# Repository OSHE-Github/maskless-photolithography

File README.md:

# Maskless Photolithography

*･゜ﾟ･*:.｡..｡.:*･'(*ﾟ▽ﾟ*)'･*:.｡. .｡.:*･゜ﾟ･*

## Copyright

- All code is licensed under the GPL 3.0 or later. You can view a copy of this license in LICENSE.code
- All hardware computer aided design "CAD files" are licensed under the CERN-OHL-S license. A copy of this license can be found in LICENSE.cad
- Some footprints are provided by the manufacturer or a third party source. They are licensed under their respective licenses.

Which licenses apply to which files will be clarified in a later commit. If you have questions please contact us.

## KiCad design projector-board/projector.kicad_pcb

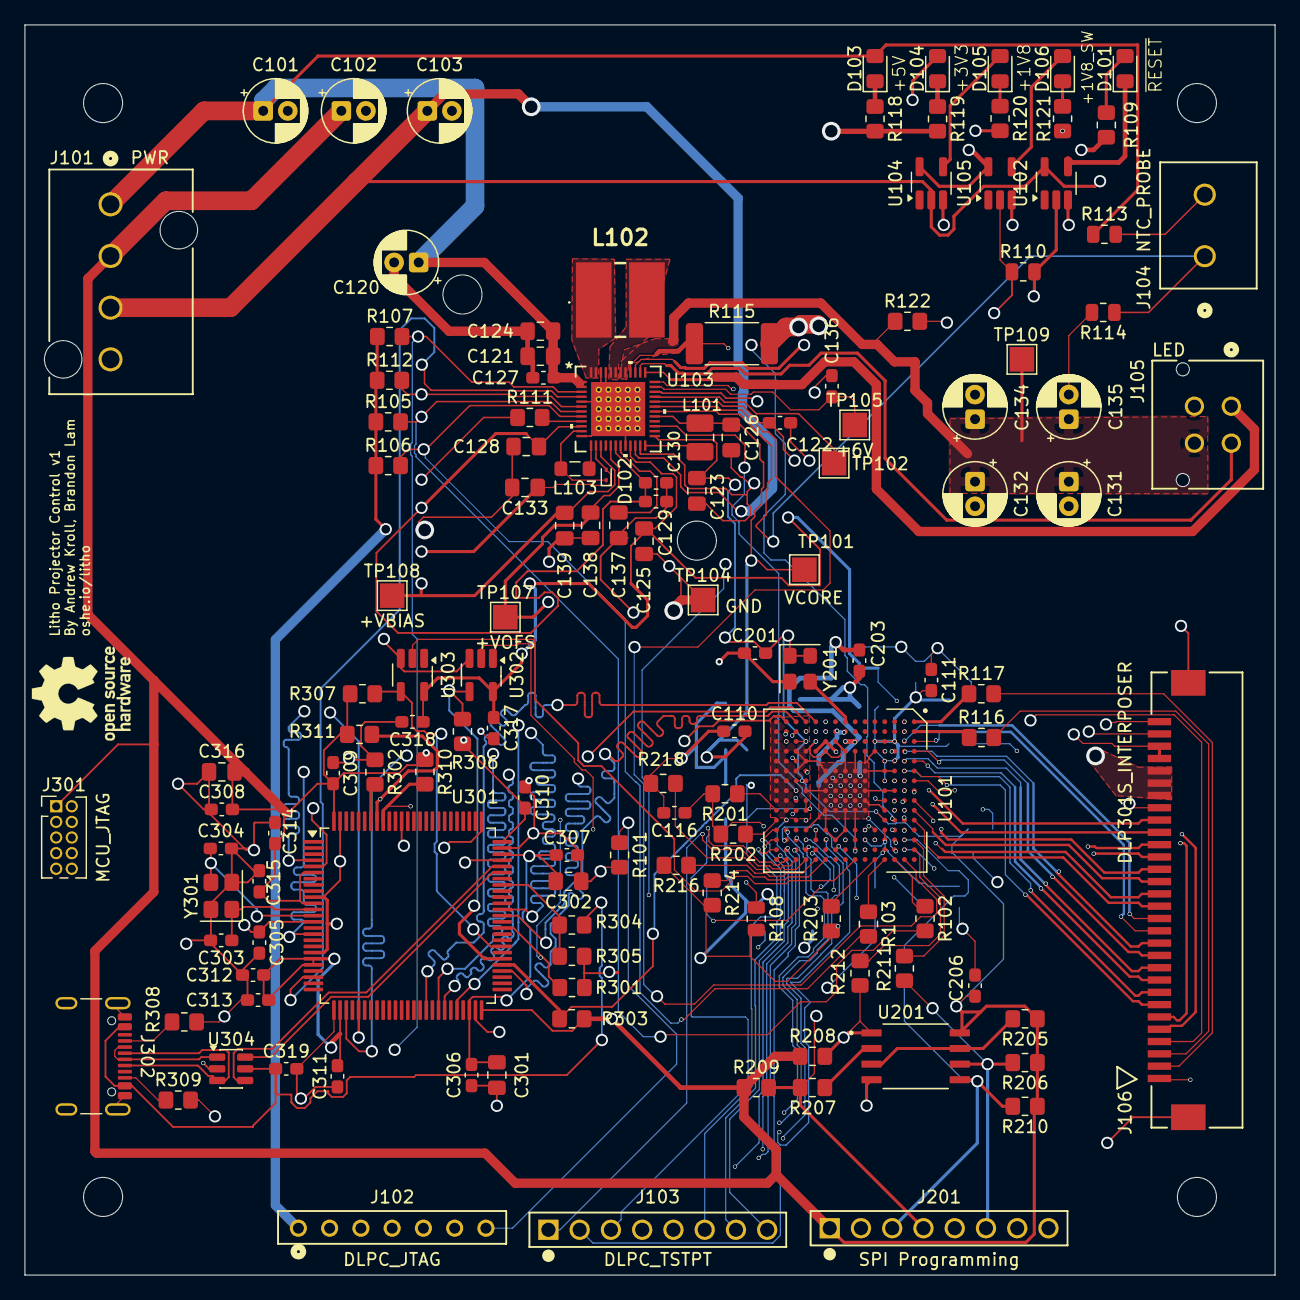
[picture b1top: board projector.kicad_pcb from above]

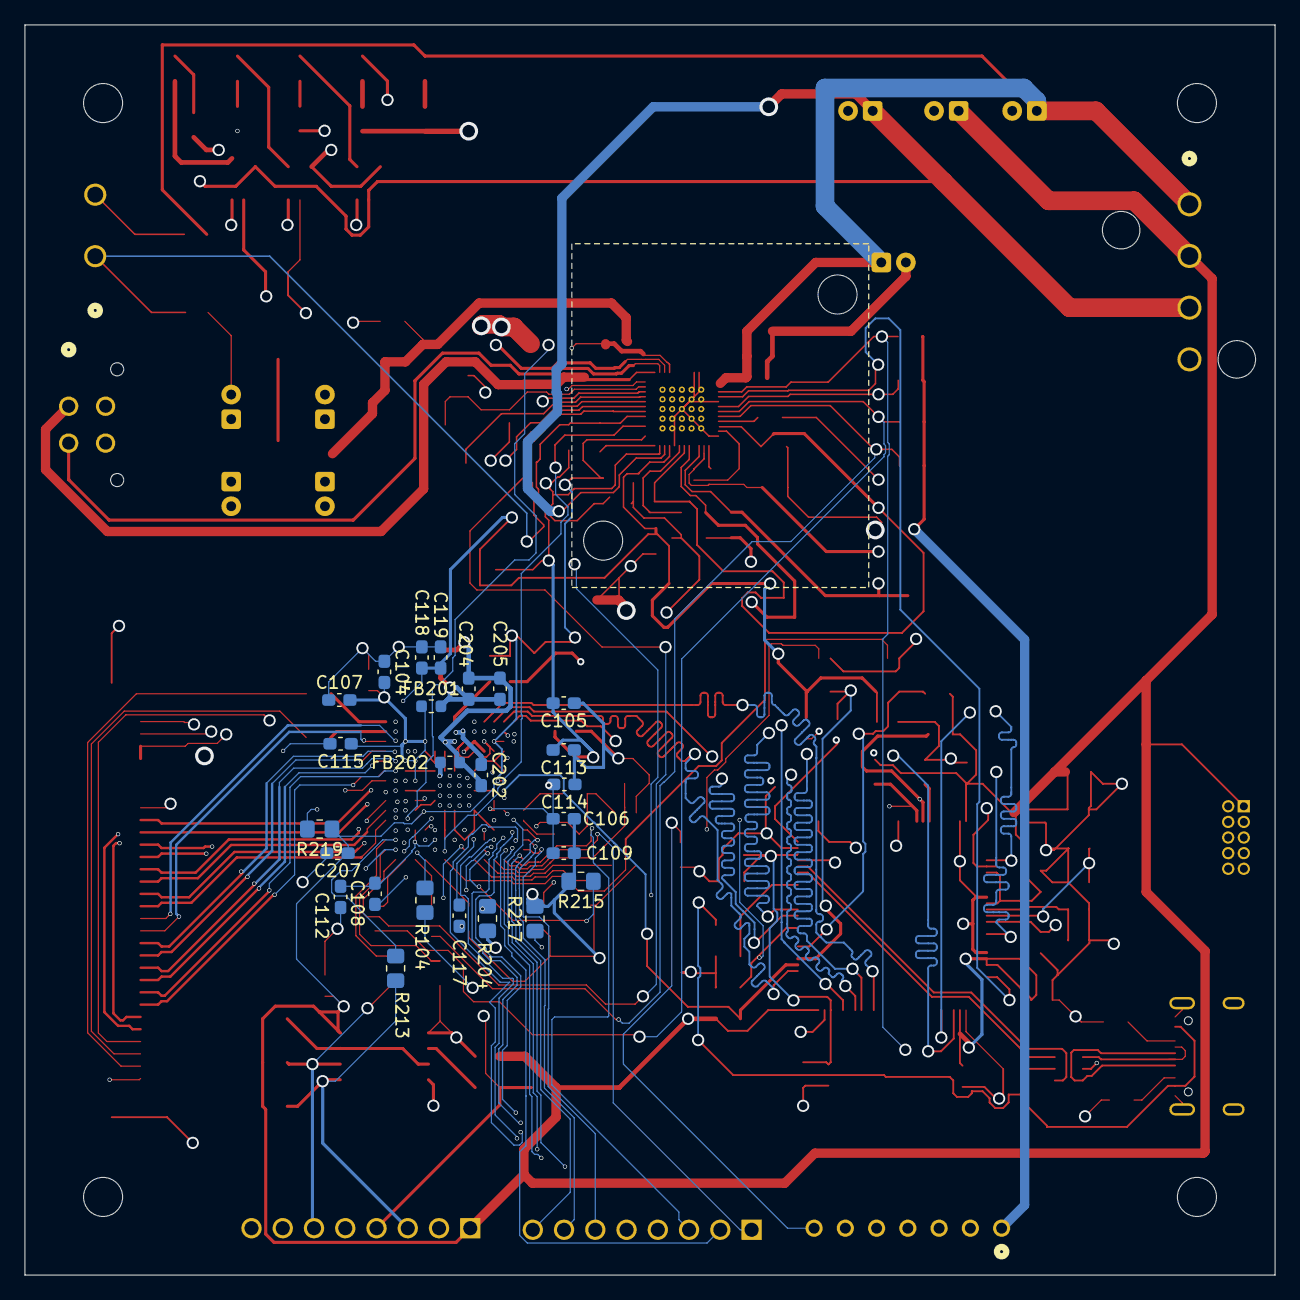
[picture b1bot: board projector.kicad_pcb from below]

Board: 4 copper layers, 101.6 x 101.6 mm, 156 parts (25 on the bottom side), 140 nets.

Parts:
C101, C102, C103: 47uF; CP_Radial_D5.0mm_P2.00mm
C104, C127, C129, C308: 1uF; C_0603_1608Metric_Pad1.08x0.95mm_HandSolder
C105, C106, C107, C108, C109, C110, C111, C112, C113, C114, C115, C116, C117, C118, C119, C122, C130, C136, C201, C203, C205, C206, C207, C305, C309, C310, C311, C312, C313, C314, C315: 0.1uF; C_0603_1608Metric_Pad1.08x0.95mm_HandSolder
C120, C131, C132, C134, C135: 22uF; CP_Radial_D5.0mm_P2.00mm
C121, C124, C125, C126, C128: 10uF; C_0805_2012Metric_Pad1.18x1.45mm_HandSolder
C123, C137, C301, C302: 2.2uF; C_0805_2012Metric_Pad1.18x1.45mm_HandSolder
C133, C138, C139: 0.22uF; C_0805_2012Metric_Pad1.18x1.45mm_HandSolder
C202, C204: 0.01uF; C_0603_1608Metric_Pad1.08x0.95mm_HandSolder
C303, C304: 12pF; C_0603_1608Metric_Pad1.08x0.95mm_HandSolder
C306, C307, C317, C318, C319: 100nF; C_0603_1608Metric_Pad1.08x0.95mm_HandSolder
C316: 4.7uF; C_0805_2012Metric_Pad1.18x1.45mm_HandSolder
D101, D103, D104, D105, D106: RED; D_0805_2012Metric_Pad1.15x1.40mm_HandSolder
D102: RB720M-30_R1_00001; D_SOD-923
FB201, FB202: BLM18EG601SN1D; L_0603_1608Metric
J101: PWR; CONN_55660001-SD_04_MOL
J102: DLPC_JTAG; CON7_1X7_TU_TSW
J103: DLPC_TSTPT; CONN8_61300811121_WRE
J104: NTC_PROBE; CONN2_710002_WRE
J105: LED; CONN_SD-43045-010_04_MOL
J106: DMD; CON_522713079_MOL
J201: SPI Programming; CONN8_61300811121_WRE
J301: MCU_JTAG; PinHeader_2x05_P1.27mm_Vertical
J302: USB4105-GF-A; USB_C_Receptacle_GCT_USB4105-xx-A_16P_TopMnt_Horizontal
L101: 2.2uH; L_1008_2520Metric_Pad1.43x2.20mm_HandSolder
L102: 2.2uH; SDCHA1V60451R2R
L103: 10uH; L_0805_2012Metric_Pad1.05x1.20mm_HandSolder
R101, R112, R301, R302, R306, R307: 10k; R_0805_2012Metric_Pad1.20x1.40mm_HandSolder
R102, R103, R104, R111, R207, R211, R212, R213: 30.1; R_0805_2012Metric_Pad1.20x1.40mm_HandSolder
R105, R106, R107, R122: 100k; R_0805_2012Metric_Pad1.20x1.40mm_HandSolder
R108: 0; R_0805_2012Metric
R109, R118, R119, R120, R121: 510; R_0805_2012Metric_Pad1.20x1.40mm_HandSolder
R110, R113, R114: DNL; R_0805_2012Metric
R115: 39m, 3 W; R_2512_6332Metric_Pad1.40x3.35mm_HandSolder
R116, R117: 43; R_0805_2012Metric_Pad1.20x1.40mm_HandSolder
R201, R202, R203, R204, R205, R206, R208, R209, R210, R214, R215, R216, R217, R218, R219, R303, R310, R311: 4.7k; R_0805_2012Metric_Pad1.20x1.40mm_HandSolder
R304: 33k; R_0805_2012Metric_Pad1.20x1.40mm_HandSolder
R305: 82k; R_0805_2012Metric_Pad1.20x1.40mm_HandSolder
R308, R309: 5.1k; R_0805_2012Metric_Pad1.20x1.40mm_HandSolder
TP101: VCORE; TestPoint_Pad_2.0x2.0mm
TP102: SENS1; TestPoint_Pad_2.0x2.0mm
TP104: GND; TestPoint_Pad_2.0x2.0mm
TP105: +6V; TestPoint_Pad_2.0x2.0mm
TP107: +VOFS; TestPoint_Pad_2.0x2.0mm
TP108: +VBIAS; TestPoint_Pad_2.0x2.0mm
TP109: VLED; TestPoint_Pad_2.0x2.0mm
U101: DLPC1438; NFBGA201
U102, U104, U105, U302, U303: SN74AUP1G07DBVR; SOT-23-5_HandSoldering
U103: DLPA2005ERSLR; RSL48_4P4X4P4_TEX
U201: AT25SF321B-SHB-T; SOIC127P790X216-8N
U301: STM32H7B0VBTx; LQFP-100_14x14mm_P0.5mm
U304: USBLC6-2SC6; SOT-23-6
Y201: ASE-24.000MHZ-L-C-T; Oscillator_SMD_Abracon_ASE-4Pin_3.2x2.5mm
Y301: 25MHz; Crystal_SMD_3225-4Pin_3.2x2.5mm

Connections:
+1V8_SRC: C103.1, J101.3, U102.5 (VCC), U103.22 (LS_IN), U104.2 (A)
+1V8_SW: C116.1, C117.1, C118.1, C119.1, C122.2, C125.1, C317.1, C318.1, J102.1, J106.27, J106.28, R105.1, R106.1, R107.1, R110.1, R112.1, R201.2, R202.2, U101.C7 (VCC18), U101.C9 (VCC18), U101.D4 (VCC18), U101.E12 (VCC18), U101.F12 (VCC18), U101.K13 (VCC18), U101.M11 (VCC18), U103.21 (LS_OUT), U103.32 (VSPI), U105.2 (A), U302.5 (VCC), U303.5 (VCC)
+3V3: C102.1, C123.2, C201.2, C206.1, C207.1, C308.2, C309.2, C310.2, C311.2, C312.2, C313.2, C314.2, C315.2, C316.2, D104.2 (A), J101.2, J201.1, J301.1, R109.2, R205.1, R206.1, R208.1, R209.1, R210.1, R219.1, R303.2, R306.2, R307.2, R310.1, R311.1, U101.D11 (VCC_FLSH), U101.M3 (VCC_INTF), U101.M7 (VCC_INTF), U101.N3 (VCC_INTF), U101.N7 (VCC_INTF), U103.25 (VINC), U104.5 (VCC), U105.5 (VCC), U201.8 (VCC), U301.6 (VBAT), U301.11 (VDD), U301.20 (VREF+), U301.21 (VDDA), U301.27 (VDD), U301.50 (VDD), U301.75 (VDD), U301.100 (VDD), Y201.1 (EN), Y201.4 (Vdd)
+5V: C101.1, C120.1, C121.1, C124.1, C127.1, C128.2, C129.1, C130.2, D103.2 (A), J101.1, R113.1, U103.1 (VINL), U103.2 (VINL), U103.10 (VINR), U103.18 (VINA)
+VBIAS: C139.1, J106.30, TP108.1 (1_1), U103.15 (VBIAS)
+VCORE: C104.2, C105.2, C106.2, C107.2, C108.2, C109.2, C110.2, C111.2, C112.2, C113.2, C114.2, C115.1, C126.1, FB201.1, L101.1, TP101.1 (1_1), U101.C3 (VDDLP12), U101.C5 (VDD), U101.D3 (VDD), U101.D5 (VDD), U101.D7 (VDD), U101.D9 (VDD), U101.D12 (VDD), U101.D13 (VDD), U101.E3 (VDD), U101.F13 (VDD), U101.H13 (VDD), U101.J4 (VDD), U101.J12 (VDD), U101.K3 (VDD), U101.L4 (VDD), U101.L12 (VDD), U101.L13 (VDD), U101.M6 (VDD), U101.M9 (VDD), U101.M10 (VDD), U103.29 (VCORE)
+VOFS: C138.1, J106.29, TP107.1 (1_1), U103.17 (VOFS)
-VRST: C133.1, D102.2 (A), J106.23, U103.14 (CNTR_VRST)
/host_interface/NRST: C305.1, J301.10, U301.14 (NRST)
/host_interface/PRINT_ACTIVE_3V3: R307.1, U301.58 (PD11), U303.4 (B)
/host_interface/SWCLK: J301.4, U301.76 (PA14)
/host_interface/SWDIO: J301.2, U301.72 (PA13)
/host_interface/SWO: J301.6, U301.89 (PB3)
/host_interface/SYS_RDY_3V3: R306.1, U301.56 (PD9), U302.4 (B)
/host_interface/USB_DM: U301.70 (PA11), U304.6 (I/O1)
/host_interface/USB_DM_CONN: J302.A7 (D-), J302.B7 (D-), U304.1 (I/O1)
/host_interface/USB_DP: U301.71 (PA12), U304.4 (I/O2)
/host_interface/USB_DP_CONN: J302.A6 (D+), J302.B6 (D+), U304.3 (I/O2)
/host_interface/USB_VBUS: C319.1, J302.A4 (VBUS), J302.A9 (VBUS), J302.B4 (VBUS), J302.B9 (VBUS), R304.2, U304.5 (VBUS)
/power_and_output/DMD_DEN_ARSTZ: J106.1, U101.B1 (DMD_DEN_ARSTZ)
/power_and_output/DMD_HS_CLK_N: J106.6, U101.B7 (DMD_HS_CLK_N)
/power_and_output/DMD_HS_CLK_P: J106.5, U101.A7 (DMD_HS_CLK_P)
/power_and_output/DMD_HS_WDATA_A_N: J106.16, U101.B11 (DMD_HS_WDATA_A_N)
/power_and_output/DMD_HS_WDATA_A_P: J106.15, U101.A11 (DMD_HS_WDATA_A_P)
/power_and_output/DMD_HS_WDATA_B_N: J106.18, U101.B10 (DMD_HS_WDATA_B_N)
/power_and_output/DMD_HS_WDATA_B_P: J106.17, U101.A10 (DMD_HS_WDATA_B_P)
/power_and_output/DMD_HS_WDATA_C_N: J106.20, U101.B9 (DMD_HS_WDATA_C_N)
/power_and_output/DMD_HS_WDATA_C_P: J106.19, U101.A9 (DMD_HS_WDATA_C_P)
/power_and_output/DMD_HS_WDATA_D_N: J106.22, U101.B8 (DMD_HS_WDATA_D_N)
/power_and_output/DMD_HS_WDATA_D_P: J106.21, U101.A8 (DMD_HS_WDATA_D_P)
/power_and_output/DMD_HS_WDATA_E_N: J106.8, U101.B6 (DMD_HS_WDATA_E_N)
/power_and_output/DMD_HS_WDATA_E_P: J106.7, U101.A6 (DMD_HS_WDATA_E_P)
/power_and_output/DMD_HS_WDATA_F_N: J106.10, U101.B5 (DMD_HS_WDATA_F_N)
/power_and_output/DMD_HS_WDATA_F_P: J106.9, U101.A5 (DMD_HS_WDATA_F_P)
/power_and_output/DMD_HS_WDATA_G_N: J106.12, U101.B4 (DMD_HS_WDATA_G_N)
/power_and_output/DMD_HS_WDATA_G_P: J106.11, U101.A4 (DMD_HS_WDATA_G_P)
/power_and_output/DMD_HS_WDATA_H_N: J106.14, U101.B3 (DMD_HS_WDATA_H_N)
/power_and_output/DMD_HS_WDATA_H_P: J106.13, U101.A3 (DMD_HS_WDATA_H_P)
/power_and_output/DMD_LS_CLK: R117.1, U101.A1 (DMD_LS_CLK)
/power_and_output/DMD_LS_RDATA: J106.4, U101.B2 (DMD_LS_RDATA)
/power_and_output/DMD_LS_WDATA: R116.1, U101.A2 (DMD_LS_WDATA)
/power_and_output/LED_ANODE: C131.1, C132.1, C134.1, C135.1, J105.4, R122.1, TP109.1 (1_1), U103.41 (VLED), U103.42 (VLED)
/power_and_output/RED_CATHODE: J105.3, U103.39 (SW4)
/power_and_output/SENS_LIGHT: TP102.1 (1_1), U103.33 (SENS1)
/power_and_output/SENS_NTC: J104.1, R114.1, U103.30 (SENS2)
/power_and_output/UNUSED_CONN: J105.2, U103.38 (SW5)
/power_and_output/UV_CATHODE: J105.1, U103.37 (SW6)
/process_control/PLL_GND: C202.2, C203.2, C204.2, C205.2, FB202.1, U101.G3 (VSS_PLLM), U101.H3 (VSS_PLLD)
DATAEN_CMD: U101.P2 (DATAEN_CMD), U301.43 (PE13)
GND: C101.2, C102.2, C103.2, C104.1, C105.1, C106.1, C107.1, C108.1, C109.1, C110.1, C111.1, C112.1, C113.1, C114.1, C115.2, C116.2, C117.2, C118.2, C119.2, C120.2, C121.2, C122.1, C123.1, C124.2, C125.2, C126.2, C127.2, C128.1, C129.2, C130.1, C131.2, C132.2, C133.2, C134.2, C135.2, C136.1, C137.1, C138.2, C139.2, C201.1, C206.2, C207.2, C301.1, C302.1, C303.2, C304.2, C305.2, C306.1, C307.1, C308.1, C309.1, C310.1, C311.1, C312.1, C313.1, C314.1, C315.1, C316.1, C317.2, C318.2, C319.2, FB202.2, J101.4, J102.2, J106.24, J106.25, J106.26, J106.P1, J106.P2, J201.2, J301.3, J301.5, J301.9, J302.A1 (GND), J302.A12 (GND), J302.B1 (GND), J302.B12 (GND), J302.SH (SHIELD), R101.2, R108.2, R114.2, R115.2, R118.2, R119.2, R120.2, R121.2, R122.2, R203.1, R204.1, R214.2, R215.2, R216.2, R217.2, R218.2, R301.2, R302.1, R305.2, R308.2, R309.2, TP104.1 (1_1), U101.C4 (VSS), U101.C6 (VSS), U101.C8 (VSS), U101.D6 (VSS), U101.D8 (VSS), U101.D10 (VSS), U101.E4 (VSS), U101.E13 (VSS), U101.F4 (VSS), U101.F6 (VSS), U101.F7 (VSS), U101.F8 (VSS), U101.F9 (VSS), U101.F10 (VSS), U101.G4 (VSS), U101.G6 (VSS), U101.G7 (VSS), U101.G8 (VSS), U101.G9 (VSS), U101.G10 (VSS), U101.G12 (VSS), U101.G13 (VSS), U101.H4 (VSS), U101.H6 (VSS), U101.H7 (VSS), U101.H8 (VSS), U101.H9 (VSS), U101.H10 (VSS), U101.H12 (VSS), U101.J3 (VSS), U101.J6 (VSS), U101.J7 (VSS), U101.J8 (VSS), U101.J9 (VSS), U101.J10 (VSS), U101.J13 (VSS), U101.K4 (VSS), U101.K6 (VSS), U101.K7 (VSS), U101.K8 (VSS), U101.K9 (VSS), U101.K10 (VSS), U101.K12 (VSS), U101.L3 (VSS), U101.M4 (VSS), U101.M5 (VSS), U101.M8 (VSS), U101.M12 (VSS), U101.N4 (PDM_CVS_TE), U101.N6 (3DR), U101.P4 (PDATA_11), U101.P5 (PDATA_13), U101.P6 (PDATA_15), U101.P7 (PDATA_17), U101.P8 (PDATA_19), U101.P9 (PDATA_21), U101.P10 (PDATA_23), U101.R1 (PDATA_8), U101.R2 (PDATA_9), U101.R3 (PDATA_10), U101.R4 (PDATA_12), U101.R5 (PDATA_14), U101.R6 (PDATA_16), U101.R7 (PDATA_18), U101.R8 (PDATA_20), U101.R9 (PDATA_22), U102.3 (GND), U103.5 (AGND1), U103.12 (PGNDR), U103.20 (GND), U103.23 (PGNDC), U103.45 (PGNDL), U103.46 (PGNDL), U103.49 (EPAD), U103.V (TVIAS), U104.3 (GND), U105.3 (GND), U201.4 (GND), U301.10 (VSS), U301.19 (VSSA), U301.26 (VSS), U301.49 (VSS), U301.74 (VSS), U301.99 (VSS), U302.3 (GND), U303.3 (GND), U304.2 (GND), Y201.2 (GND), Y301.2 (G), Y301.4 (G)
HOST_IRQ: R303.1, U101.N8 (HOST_IRQ), U301.55 (PD8)
HSYNC_CS: U101.N5 (HSYNC_CS), U301.63 (PC6)
IIC0_SCL: R310.2, U101.N10 (IIC0_SCL), U301.92 (PB6)
IIC0_SDA: R311.2, U101.N9 (IIC0_SDA), U301.93 (PB7)
INTZ: R112.2, U101.C13 (PARKZ), U103.6 (INTZ)
unnamed: C301.2, C302.2, C306.2, C307.2, U301.48 (VCAP), U301.73 (VCAP)
unnamed: D101.2 (A), R109.1
unnamed: D101.1 (K), U102.4 (B)
unnamed: D102.1 (K), L103.2, U103.11 (SWN)
unnamed: D103.1 (K), R118.1
unnamed: D104.1 (K), R119.1
unnamed: D105.2 (A), U104.4 (B)
unnamed: D105.1 (K), R120.1
unnamed: D106.2 (A), U105.4 (B)
unnamed: D106.1 (K), R121.1
unnamed: J102.3, U101.P12 (JTAGTCK)
unnamed: J102.4, U101.N13 (JTAGTDO1)
unnamed: J102.5, U101.P13 (JTAGTDI)
unnamed: J102.6, U101.M13 (JTAGTMS1)
unnamed: J102.7, R101.1, U101.P11 (JTAGTRSTZ)
unnamed: J103.1, U101.N15 (TSTPT_7)
unnamed: J103.2, U101.N14 (TSTPT_6)
unnamed: J103.3, U101.P15 (TSTPT_5)
unnamed: J103.4, U101.P14 (TSTPT_4)
unnamed: J103.5, U101.R15 (TSTPT_3)
unnamed: J103.6, U101.R14 (TSTPT_2)
unnamed: J103.7, U101.R13 (TSTPT_1)
unnamed: J103.8, U101.R12 (TSTPT_0)
unnamed: J104.2, R113.2
unnamed: J106.2, R117.2
unnamed: J106.3, R116.2
unnamed: J201.3, R210.2, R213.1, U201.5 (SI(I/O0))
unnamed: J201.4, R207.2, R209.2, U101.B12 (SPI0_DIN)
unnamed: J201.5, R208.2, R212.1, U201.1 (~CS)
unnamed: J201.6, R206.2, R211.1, U201.6 (SCK)
unnamed: J302.A5 (CC1), R308.1
unnamed: J302.B5 (CC2), R309.1
unnamed: L102.1, U103.47 (L1), U103.48 (L1)
unnamed: L102.2, U103.43 (L2), U103.44 (L2)
unnamed: R108.1, U101.C10 (HWTEST_EN)
unnamed: R211.2, U101.A13 (SPI0_CLK)
unnamed: R212.2, U101.A14 (SPI0_CSZ0)
unnamed: R219.2, U101.C12 (SPI0_CSZ1)
unnamed: R213.2, U101.B13 (SPI0_DOUT)
unnamed: U101.H1 (PLL_REFCLK_I), Y201.3 (OUT)
unnamed: C202.1, C203.1, C204.1, C205.1, FB201.2, U101.H2 (VDD_PLLM), U101.J2 (VDD_PLLD)
unnamed: R202.1, U101.R11 (IIC1_SCL)
unnamed: R201.1, U101.R10 (IIC1_SDA)
unnamed: R111.1, U101.C14 (GPIO_00/SPI1_DIN)
unnamed: R102.1, U101.C15 (GPIO_01/SPI1_CLK)
unnamed: R104.1, U101.D14 (GPIO_02/SPI1_DOUT)
unnamed: R103.1, U101.D15 (GPIO_03/SPI1_CSZ0)
unnamed: U101.B15 (LED_SEL_0), U103.31 (LED_SEL0)
unnamed: U101.B14 (LED_SEL_1), U103.34 (LED_SEL1)
unnamed: R203.2, U101.E15 (GPIO_05)
unnamed: R204.2, U101.J14 (GPIO_12)
unnamed: R214.1, U101.K15 (GPIO_15)
unnamed: R215.1, U101.L14 (GPIO_16)
unnamed: R216.1, U101.L15 (GPIO_17)
unnamed: R217.1, U101.M14 (GPIO_18)
unnamed: R218.1, U101.M15 (GPIO_19)
unnamed: R115.1, U103.36 (RLIM_K), U103.40 (RLIM)
unnamed: R102.2, R105.2, U103.7 (SPI_CLK)
unnamed: R103.2, R106.2, U103.8 (SPI_CSZ)
unnamed: R104.2, R107.2, U103.3 (SPI_DIN)
unnamed: R111.2, U103.9 (SPI_DOUT)
unnamed: L101.2, U103.24 (SWC)
unnamed: L103.1, U103.13 (SWP)
unnamed: C137.2, U103.19 (V2V5)
unnamed: C136.2, TP105.1 (1_1), U103.35 (V6V)
unnamed: R207.1, U201.2 (SO(I/O1))
unnamed: R205.2, U201.3 (~WP(I/O2)), U201.7 (~HOLD/~RESET(I/O3))
unnamed: R302.2, U301.94 (BOOT0)
unnamed: R304.1, R305.1, U301.68 (PA9)
unnamed: C303.1, U301.12 (PH0), Y301.1
unnamed: C304.1, U301.13 (PH1), Y301.3
PCLK: U101.P3 (PCLK), U301.44 (PE14)
PDATA_0: U101.K2 (PDATA_0), U301.4 (PE5)
PDATA_1: U101.K1 (PDATA_1), U301.5 (PE6)
PDATA_2: U101.L2 (PDATA_2), U301.30 (PA6)
PDATA_3: U101.L1 (PDATA_3), U301.41 (PE11)
PDATA_4: U101.M2 (PDATA_4), U301.46 (PB10)
PDATA_5: U101.M1 (PDATA_5), U301.16 (PC1)
PDATA_6: U101.N2 (PDATA_6), U301.64 (PC7)
PDATA_7: U101.N1 (PDATA_7), U301.54 (PB15)
PRINT_ACTIVE: U101.G15 (GPIO_09/PRINT_ACTIVE), U303.2 (A)
PROJ_ON: R301.1, U101.G14 (GPIO_08/PARK), U103.27 (PROJ_ON), U301.61 (PD14)
SYS_RDY: U101.F14 (GPIO_06/SYSTEM_READY), U302.2 (A)
VSYNC_WE: U101.P1 (VSYNC_WE), U301.28 (PA4)
~RESETZ: R110.2, U101.C11 (RESETZ), U102.2 (A), U103.4 (RESETZ), U301.23 (PA1)

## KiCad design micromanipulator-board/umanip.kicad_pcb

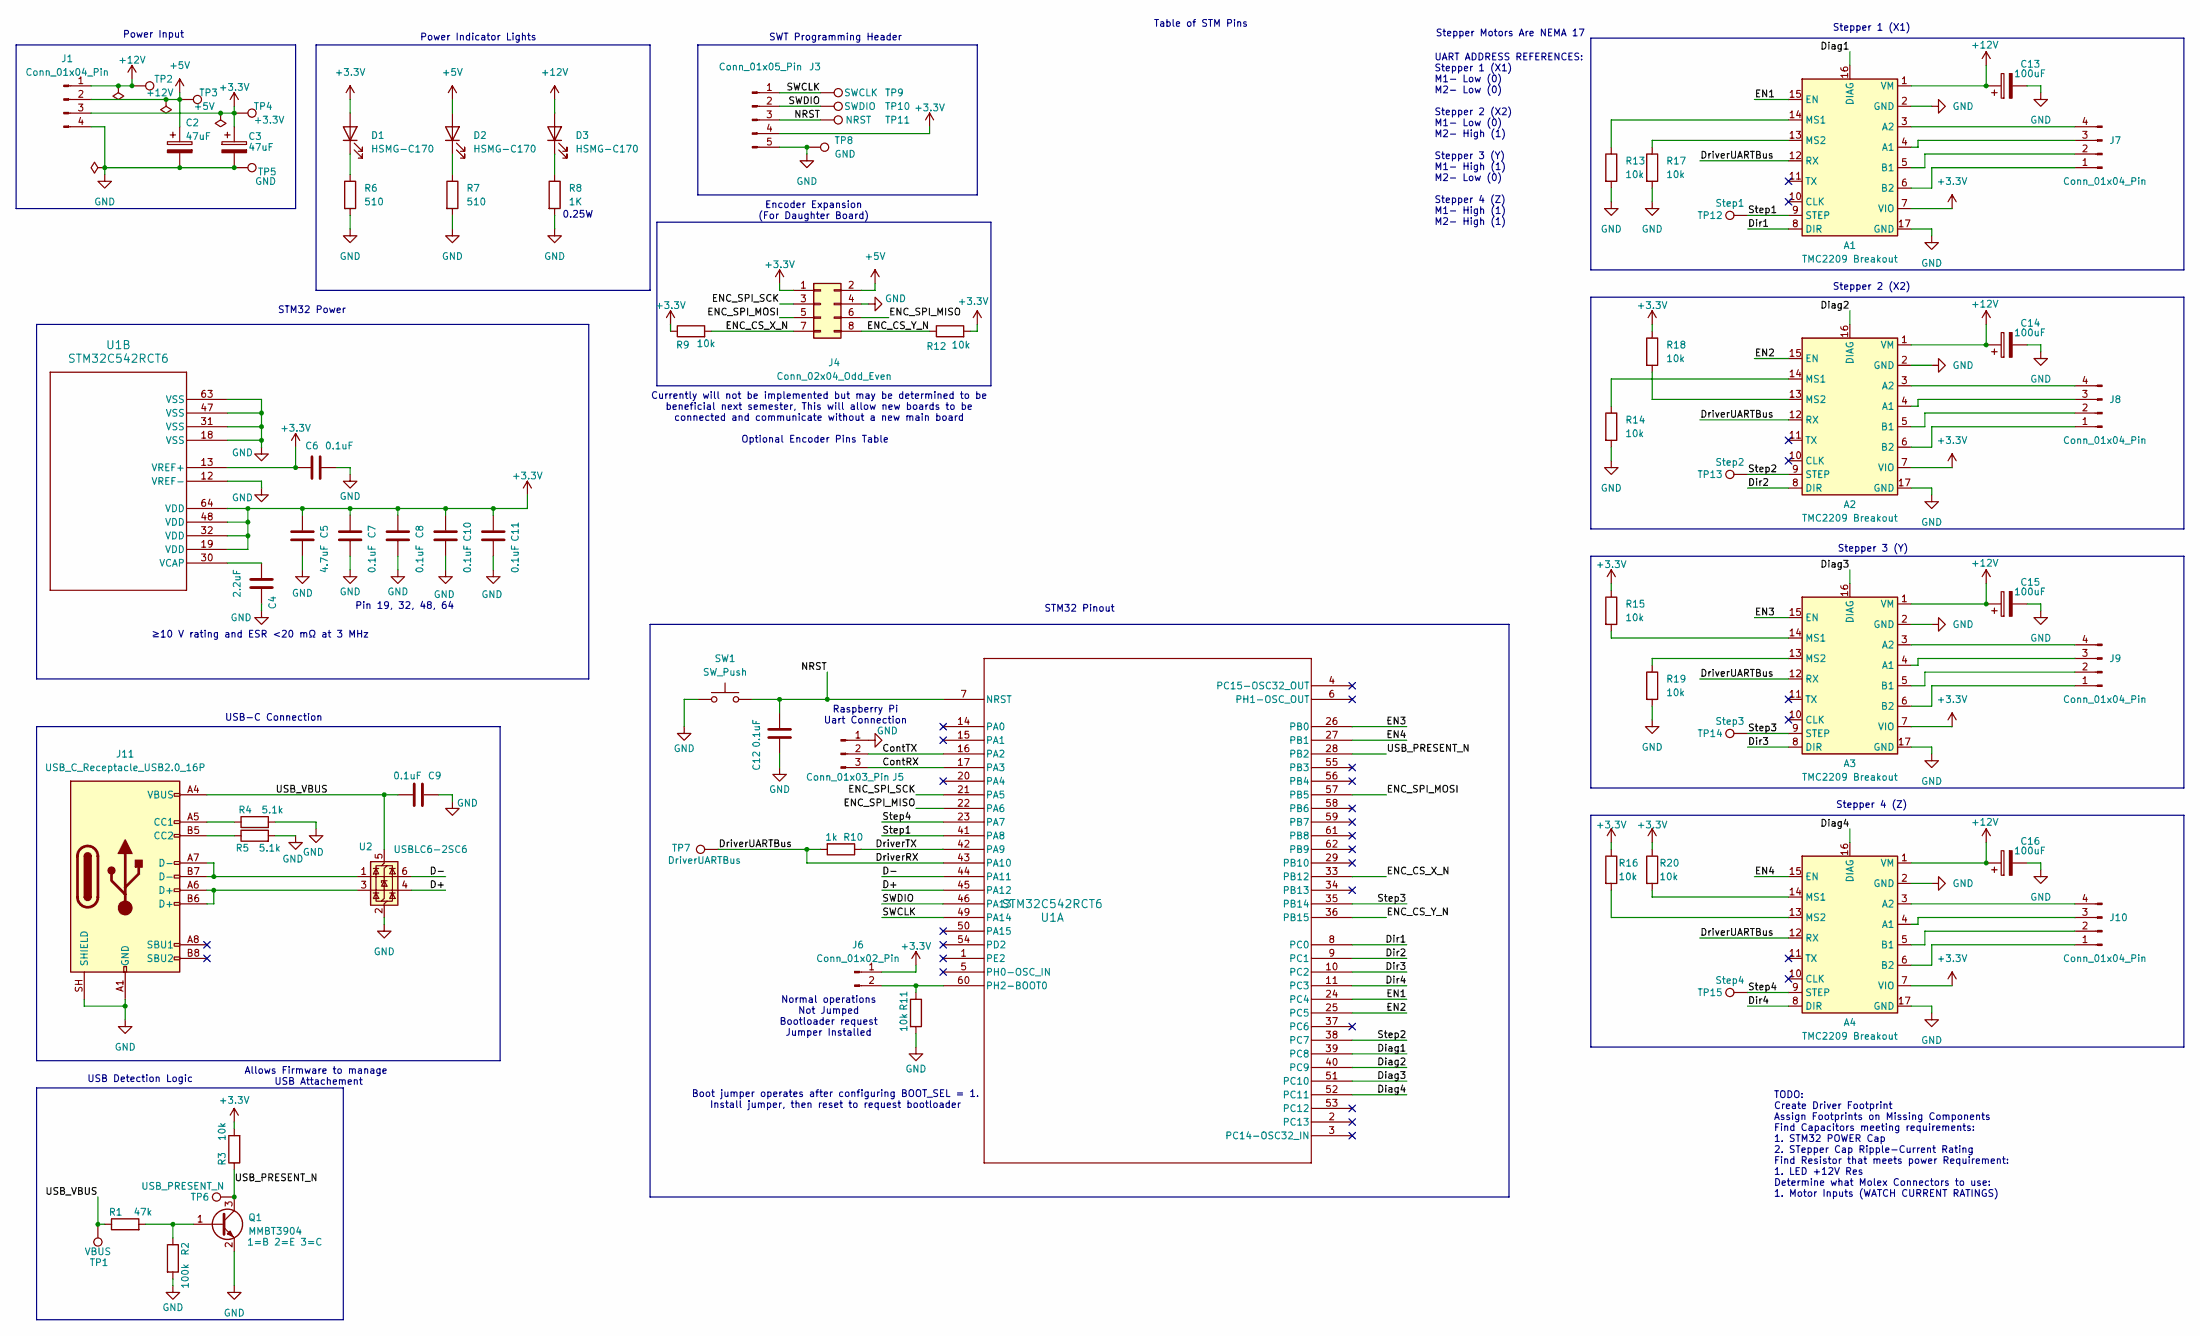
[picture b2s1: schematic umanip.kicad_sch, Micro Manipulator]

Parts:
A1, A2, A3, A4: TMC2209 Breakout; BIGTREETECH__TMC2209_17.2x20.3mm
C2, C3: 47uF; CP_Radial_D5.0mm_P2.00mm; Digikey 732-8789-1-ND
C4: 2.2uF; C_0603_1608Metric_Pad1.08x0.95mm_HandSolder; Digikey 4713-GMC10X7R104K50NTCT-ND
C5: 4.7uF; C_0603_1608Metric_Pad1.08x0.95mm_HandSolder; Digikey 4713-GMC10X7R104K50NTCT-ND
C6, C7, C8, C9, C10, C11, C12: 0.1uF; C_0603_1608Metric_Pad1.08x0.95mm_HandSolder; Digikey 4713-GMC10X7R104K50NTCT-ND
C13, C14, C15, C16: 100uF; CP_Radial_D5.0mm_P2.00mm; Digikey 732-8789-1-ND
D1, D2, D3: HSMG-C170; D_0805_2012Metric_Pad1.15x1.40mm_HandSolder; Digikey 516-1434-1-ND
J1: Conn_01x04_Pin; CONN_55660001-SD_04_MOL
J3: Conn_01x05_Pin; Molex_Micro-Fit_3.0_43650-0515_1x05_P3.00mm_Vertical
J4: Conn_02x04_Odd_Even; Molex_Micro-Fit_3.0_43045-0812_2x04_P3.00mm_Vertical
J5: Conn_01x03_Pin; Molex_Micro-Fit_3.0_43650-0315_1x03_P3.00mm_Vertical
J6: Conn_01x02_Pin; PinHeader_1x02_P2.54mm_Vertical
J7, J8, J9, J10: Conn_01x04_Pin; Molex_Micro-Fit_3.0_43650-0415_1x04_P3.00mm_Vertical
J11: USB_C_Receptacle_USB2.0_16P; USB_C_Receptacle_GCT_USB4105-xx-A_16P_TopMnt_Horizontal
Q1: MMBT3904; SOT-23
R1: 47k; R_0805_2012Metric_Pad1.20x1.40mm_HandSolder
R2: 100k; R_0805_2012Metric_Pad1.20x1.40mm_HandSolder
R3, R9, R11, R12, R13, R14, R15, R16, R17, R18, R19, R20: 10k; R_0805_2012Metric_Pad1.20x1.40mm_HandSolder
R4, R5: 5.1k; R_0805_2012Metric_Pad1.20x1.40mm_HandSolder
R6, R7: 510; R_0805_2012Metric_Pad1.20x1.40mm_HandSolder; Digikey 13-RT0805FRE07510RLCT-ND
R8: 1K; R_0805_2012Metric_Pad1.20x1.40mm_HandSolder; Digikey 13-RT0805FRE07510RLCT-ND
R10: 1k; R_0805_2012Metric_Pad1.20x1.40mm_HandSolder
SW1: SW_Push; SW_PUSH_6mm
TP1: VBUS; TestPoint_Pad_D2.0mm
TP2: +12V; TestPoint_Pad_D2.0mm
TP3: +5V; TestPoint_Pad_D2.0mm
TP4: +3.3V; TestPoint_Pad_D2.0mm
TP5, TP8: GND; TestPoint_Pad_D2.0mm
TP6: USB_PRESENT_N; TestPoint_Pad_D2.0mm
TP7: DriverUARTBus; TestPoint_Pad_D2.0mm
TP9: SWCLK; TestPoint_Pad_D2.0mm
TP10: SWDIO; TestPoint_Pad_D2.0mm
TP11: NRST; TestPoint_Pad_D2.0mm
TP12: Step1; TestPoint_Pad_D2.0mm
TP13: Step2; TestPoint_Pad_D2.0mm
TP14: Step3; TestPoint_Pad_D2.0mm
TP15: Step4; TestPoint_Pad_D2.0mm
U1: STM32C542RCT6; LQFP64_STM
U2: USBLC6-2SC6; SOT-23-6

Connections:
+3.3V: A1.7 (VIO), A2.7 (VIO), A3.7 (VIO), A4.7 (VIO), C3.1, C5.1, C6.1, C7.1, C8.1, C10.1, C11.1, D1.2 (A), J1.3, J3.4, J4.1, J6.1, R3.2, R9.1, R12.2, R15.1, R16.1, R18.1, R20.1, TP4.1 (1_1), U1.13 (VREF+), U1.19 (VDD), U1.32 (VDD), U1.48 (VDD), U1.64 (VDD)
+5V: C2.1, D2.2 (A), J1.2, J4.2, TP3.1 (1_1)
+12V: A1.1 (VM), A2.1 (VM), A3.1 (VM), A4.1 (VM), C13.1, C14.1, C15.1, C16.1, D3.2 (A), J1.1, TP2.1 (1_1)
/ContRX: J5.3, U1.17 (PA3)
/ContTX: J5.2, U1.16 (PA2)
/D+: U1.45 (PA12), U2.4 (I/O2)
/D-: U1.44 (PA11), U2.6 (I/O1)
/Diag1: A1.16 (DIAG), U1.39 (PC8)
/Diag2: A2.16 (DIAG), U1.40 (PC9)
/Diag3: A3.16 (DIAG), U1.51 (PC10)
/Diag4: A4.16 (DIAG), U1.52 (PC11)
/Dir1: A1.8 (DIR), U1.8 (PC0)
/Dir2: A2.8 (DIR), U1.9 (PC1)
/Dir3: A3.8 (DIR), U1.10 (PC2)
/Dir4: A4.8 (DIR), U1.11 (PC3)
/DriverRX: A1.12 (RX), A2.12 (RX), A3.12 (RX), A4.12 (RX), R10.2, TP7.1 (1_1), U1.43 (PA10)
/DriverTX: R10.1, U1.42 (PA9)
/EN1: A1.15 (EN), U1.24 (PC4)
/EN2: A2.15 (EN), U1.25 (PC5)
/EN3: A3.15 (EN), U1.26 (PB0)
/EN4: A4.15 (EN), U1.27 (PB1)
/ENC_CS_X_N: J4.7, R9.2, U1.33 (PB12)
/ENC_CS_Y_N: J4.8, R12.1, U1.36 (PB15)
/ENC_SPI_MISO: J4.6, U1.22 (PA6)
/ENC_SPI_MOSI: J4.5, U1.57 (PB5)
/ENC_SPI_SCK: J4.3, U1.21 (PA5)
/NRST: C12.2, J3.3, SW1.2, TP11.1 (1_1), U1.7 (NRST)
/SWCLK: J3.1, TP9.1 (1_1), U1.49 (PA14)
/SWDIO: J3.2, TP10.1 (1_1), U1.46 (PA13)
/Step1: A1.9 (STEP), TP12.1 (1_1), U1.41 (PA8)
/Step2: A2.9 (STEP), TP13.1 (1_1), U1.38 (PC7)
/Step3: A3.9 (STEP), TP14.1 (1_1), U1.35 (PB14)
/Step4: A4.9 (STEP), TP15.1 (1_1), U1.23 (PA7)
/USB_PRESENT_N: Q1.3 (C), R3.1, TP6.1 (1_1), U1.28 (PB2)
/USB_VBUS: C9.2, J11.A4 (VBUS), J11.A9 (VBUS), J11.B4 (VBUS), J11.B9 (VBUS), R1.1, TP1.1 (1_1), U2.5 (VBUS)
GND: A1.2 (GND), A1.17 (GND), A2.2 (GND), A2.17 (GND), A3.2 (GND), A3.17 (GND), A4.2 (GND), A4.17 (GND), C2.2, C3.2, C4.2, C5.2, C6.2, C7.2, C8.2, C9.1, C10.2, C11.2, C12.1, C13.2, C14.2, C15.2, C16.2, J1.4, J3.5, J4.4, J5.1, J11.A1 (GND), J11.A12 (GND), J11.B1 (GND), J11.B12 (GND), J11.SH (SHIELD), Q1.2 (E), R2.2, R4.2, R5.2, R6.2, R7.2, R8.2, R11.2, R13.2, R14.2, R17.2, R19.2, SW1.1, TP5.1 (1_1), TP8.1 (1_1), U1.12 (VREF-), U1.18 (VSS), U1.31 (VSS), U1.47 (VSS), U1.63 (VSS), U2.2 (GND)
unnamed: A1.4 (A1), J7.3
unnamed: A1.3 (A2), J7.4
unnamed: A1.5 (B1), J7.2
unnamed: A1.6 (B2), J7.1
unnamed: A1.14 (MS1), R13.1
unnamed: A1.13 (MS2), R17.1
unnamed: A2.4 (A1), J8.3
unnamed: A2.3 (A2), J8.4
unnamed: A2.5 (B1), J8.2
unnamed: A2.6 (B2), J8.1
unnamed: A2.14 (MS1), R14.1
unnamed: A2.13 (MS2), R18.2
unnamed: A3.4 (A1), J9.3
unnamed: A3.3 (A2), J9.4
unnamed: A3.5 (B1), J9.2
unnamed: A3.6 (B2), J9.1
unnamed: A3.14 (MS1), R15.2
unnamed: A3.13 (MS2), R19.1
unnamed: A4.4 (A1), J10.3
unnamed: A4.3 (A2), J10.4
unnamed: A4.5 (B1), J10.2
unnamed: A4.6 (B2), J10.1
unnamed: A4.14 (MS1), R20.2
unnamed: A4.13 (MS2), R16.2
unnamed: D1.1 (K), R6.1
unnamed: D2.1 (K), R7.1
unnamed: D3.1 (K), R8.1
unnamed: J6.2, R11.1, U1.60 (PH2-BOOT0)
unnamed: J11.A5 (CC1), R4.1
unnamed: J11.B5 (CC2), R5.1
unnamed: J11.A6 (D+), J11.B6 (D+), U2.3 (I/O2)
unnamed: J11.A7 (D-), J11.B7 (D-), U2.1 (I/O1)
unnamed: Q1.1 (B), R1.2, R2.1
unnamed: C4.1, U1.30 (VCAP)

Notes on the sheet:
TODO: Create Driver Footprint Assign Footprints on Missing Components Find Capacitors meeting requirements: 1. STM32 POWER Cap 2. STepper Cap Ripple-Current Rating Find Resistor that meets power Requirement: 1. LED +12V Res Determine what Molex Connectors to use: 1. Motor Inputs (WATCH CURRENT RATI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
Stepper 3 (Y)
Stepper Motors Are NEMA 17
Pin 19, 32, 48, 64
USB-C Connection
Allows Firmware to manage USB Attachement
STM32 Pinout
Power Indicator Lights
Table of STM Pins
Stepper 2 (X2)
UART ADDRESS REFERENCES: Stepper 1 (X1) M1- Low (0) M2- Low (0) Stepper 2 (X2) M1- Low (0) M2- High (1) Stepper 3 (Y) M1- High (1) M2- Low (0) Stepper 4 (Z) M1- High (1) M2- High (1)
Currently will not be implemented but may be determined to be beneficial next semester, This will allow new boards to be connected and communicate without a new main board
Optional Encoder Pins Table
Boot jumper operates after configuring BOOT_SEL = 1. Install jumper, then reset to request bootloader
Stepper 1 (X1)
Encoder Expansion (For Daughter Board)
Normal operations Not Jumped Bootloader request Jumper Installed
USB Detection Logic
Power Input
STM32 Power
0.25W
≥10 V rating and ESR <20 mΩ at 3 MHz
Raspberry Pi Uart Connection
SWT Programming Header
Stepper 4 (Z)

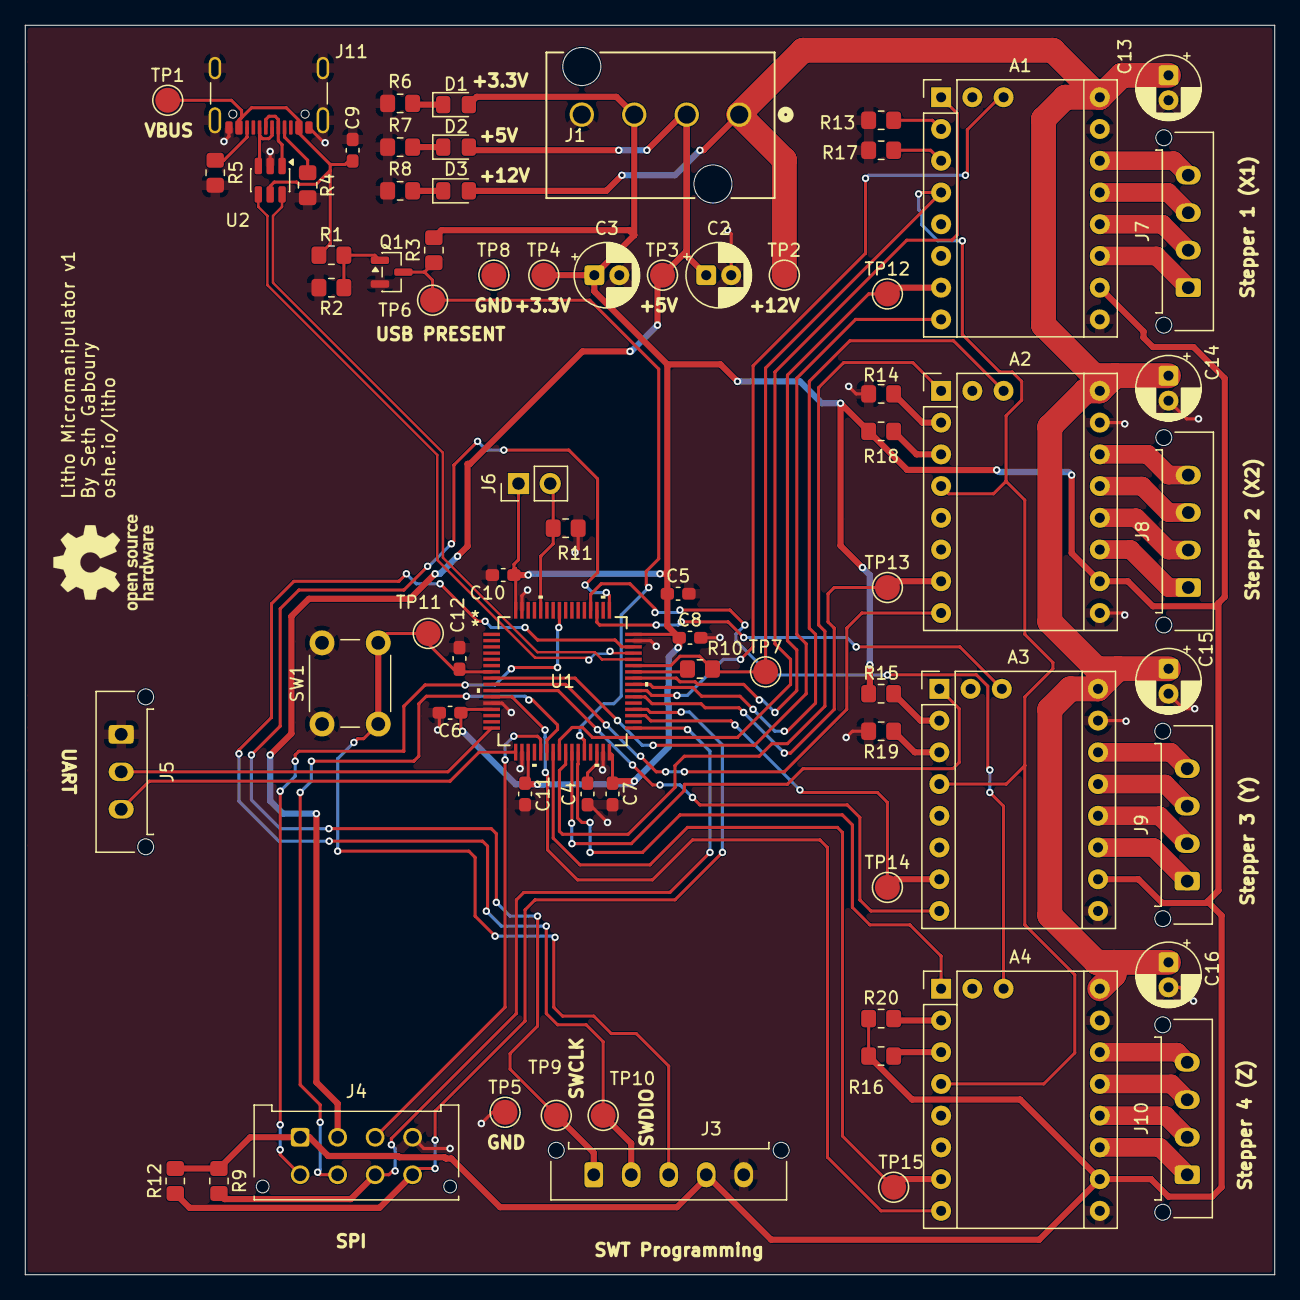
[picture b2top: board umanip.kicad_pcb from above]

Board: 2 copper layers, 100.0 x 100.0 mm, 71 parts (0 on the bottom side), 70 nets.

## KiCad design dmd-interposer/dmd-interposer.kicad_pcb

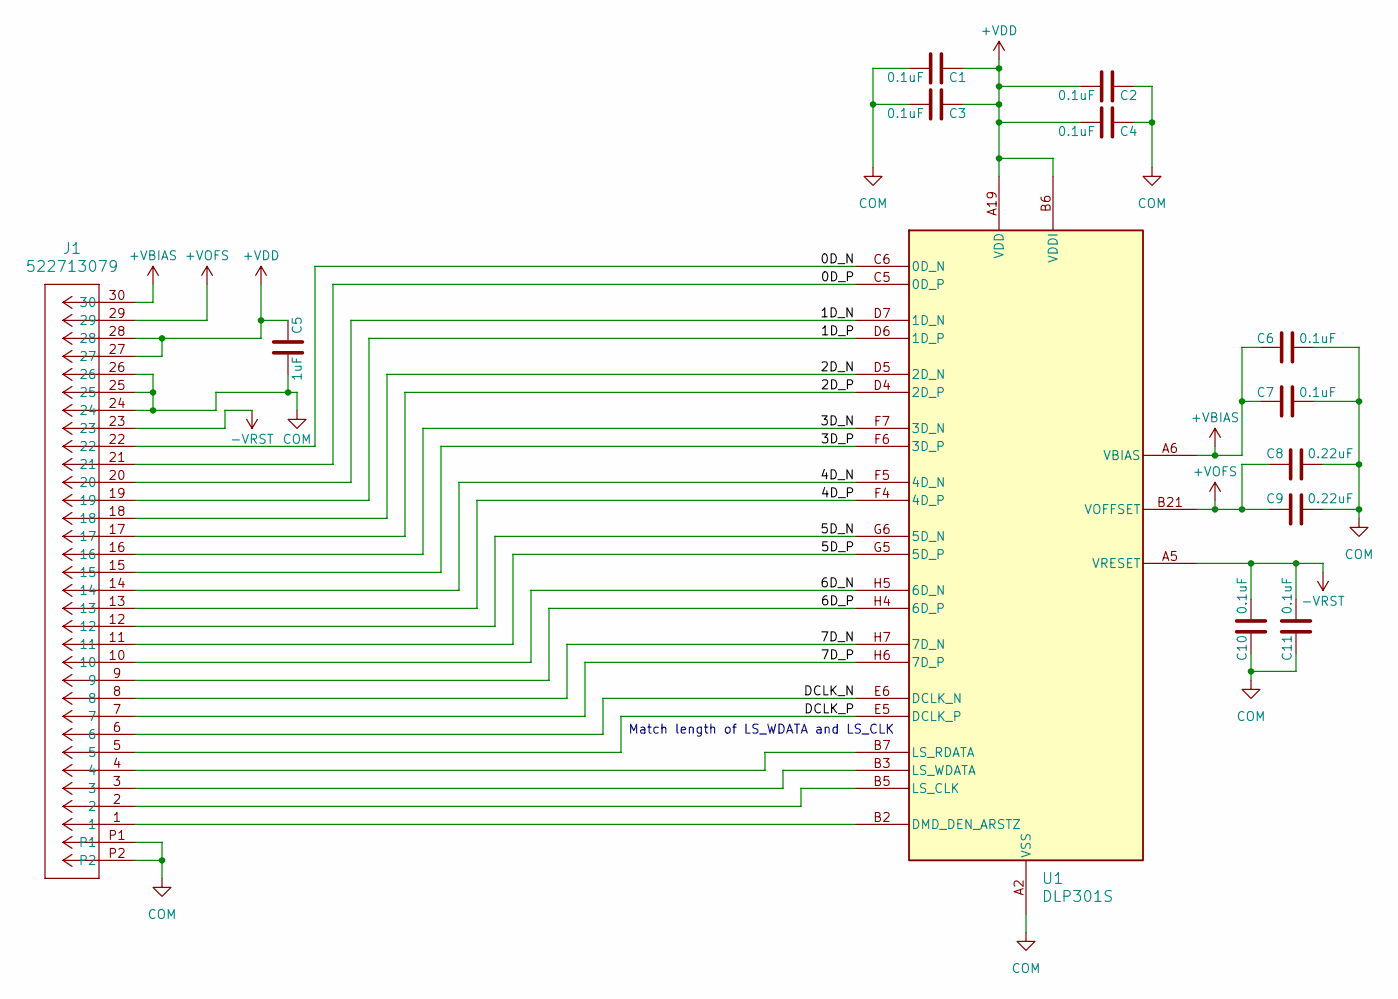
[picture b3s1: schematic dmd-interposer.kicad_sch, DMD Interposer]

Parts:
C1, C2, C3, C4, C6, C7, C10, C11: 0.1uF; C_0603_1608Metric_Pad1.08x0.95mm_HandSolder; Digikey 4713-GMC10X7R104K50NTCT-ND
C5: 1uF; C_0603_1608Metric_Pad1.08x0.95mm_HandSolder; Digikey 1276-1946-1-ND
C8, C9: 0.22uF; C_0805_2012Metric_Pad1.18x1.45mm_HandSolder; Digikey 1276-CL21B224KBFNNNFCT-ND
J1: 522713079; CON_522713079_MOL
U1: DLP301S; PCB_OUTLINE_DLP301S_INTERPOSER

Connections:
+VBIAS: C6.1, C7.1, J1.30, U1.A6 (VBIAS), U1.A22 (VBIAS)
+VDD: C1.1, C2.2, C3.1, C4.2, C5.1, J1.27, J1.28, U1.A19 (VDD), U1.A20 (VDD), U1.A21 (VDD), U1.B6 (VDDI), U1.B19 (VDDI), U1.B20 (VDD), U1.C2 (VDD), U1.C3 (VDDI), U1.C23 (VDDI), U1.D2 (VDD), U1.D3 (VDD), U1.D23 (VDD), U1.E2 (VDD), U1.E3 (VDDI), U1.E23 (VDDI), U1.F2 (VDD), U1.F3 (VDD), U1.F23 (VDD), U1.G3 (VDDI), U1.G23 (VDDI)
+VOFS: C8.2, C9.2, J1.29, U1.B21 (VOFFSET), U1.G2 (VOFFSET)
-VRST: C10.2, C11.2, J1.23, U1.A5 (VRESET), U1.A23 (VRESET)
/0D_N: J1.22, U1.C6 (0D_N)
/0D_P: J1.21, U1.C5 (0D_P)
/1D_N: J1.20, U1.D7 (1D_N)
/1D_P: J1.19, U1.D6 (1D_P)
/2D_N: J1.18, U1.D5 (2D_N)
/2D_P: J1.17, U1.D4 (2D_P)
/3D_N: J1.16, U1.F7 (3D_N)
/3D_P: J1.15, U1.F6 (3D_P)
/4D_N: J1.14, U1.F5 (4D_N)
/4D_P: J1.13, U1.F4 (4D_P)
/5D_N: J1.12, U1.G6 (5D_N)
/5D_P: J1.11, U1.G5 (5D_P)
/6D_N: J1.10, U1.H5 (6D_N)
/6D_P: J1.9, U1.H4 (6D_P)
/7D_N: J1.8, U1.H7 (7D_N)
/7D_P: J1.7, U1.H6 (7D_P)
/DCLK_N: J1.6, U1.E6 (DCLK_N)
/DCLK_P: J1.5, U1.E5 (DCLK_P)
COM: C1.2, C2.1, C3.2, C4.1, C5.2, C6.2, C7.2, C8.1, C9.1, C10.1, C11.1, J1.24, J1.25, J1.26, J1.P1, J1.P2, U1.A2 (VSS), U1.A3 (VSS), U1.A4 (VSS), U1.A7 (VSS), U1.A24 (VSS), U1.B22 (VSS), U1.B23 (VSS), U1.B24 (VSS), U1.C4 (VSS), U1.C7 (VSS), U1.C19 (VSS), U1.C22 (VSS), U1.E4 (VSS), U1.E7 (VSS), U1.E19 (VSS), U1.E22 (VSS), U1.G4 (VSS), U1.G7 (VSS), U1.G19 (VSS), U1.G22 (VSS), U1.G24 (VSS), U1.H2 (VSS), U1.H3 (VSS), U1.H23 (VSS), U1.H24 (VSS)
unnamed: J1.1, U1.B2 (DMD_DEN_ARSTZ)
unnamed: J1.2, U1.B5 (LS_CLK)
unnamed: J1.4, U1.B7 (LS_RDATA)
unnamed: J1.3, U1.B3 (LS_WDATA)

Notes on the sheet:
Match length of LS_WDATA and LS_CLK
